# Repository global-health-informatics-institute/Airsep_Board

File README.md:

# Airsep_Board
Contains schematic design for the PCB, Eagle PCB design and MPLABX code

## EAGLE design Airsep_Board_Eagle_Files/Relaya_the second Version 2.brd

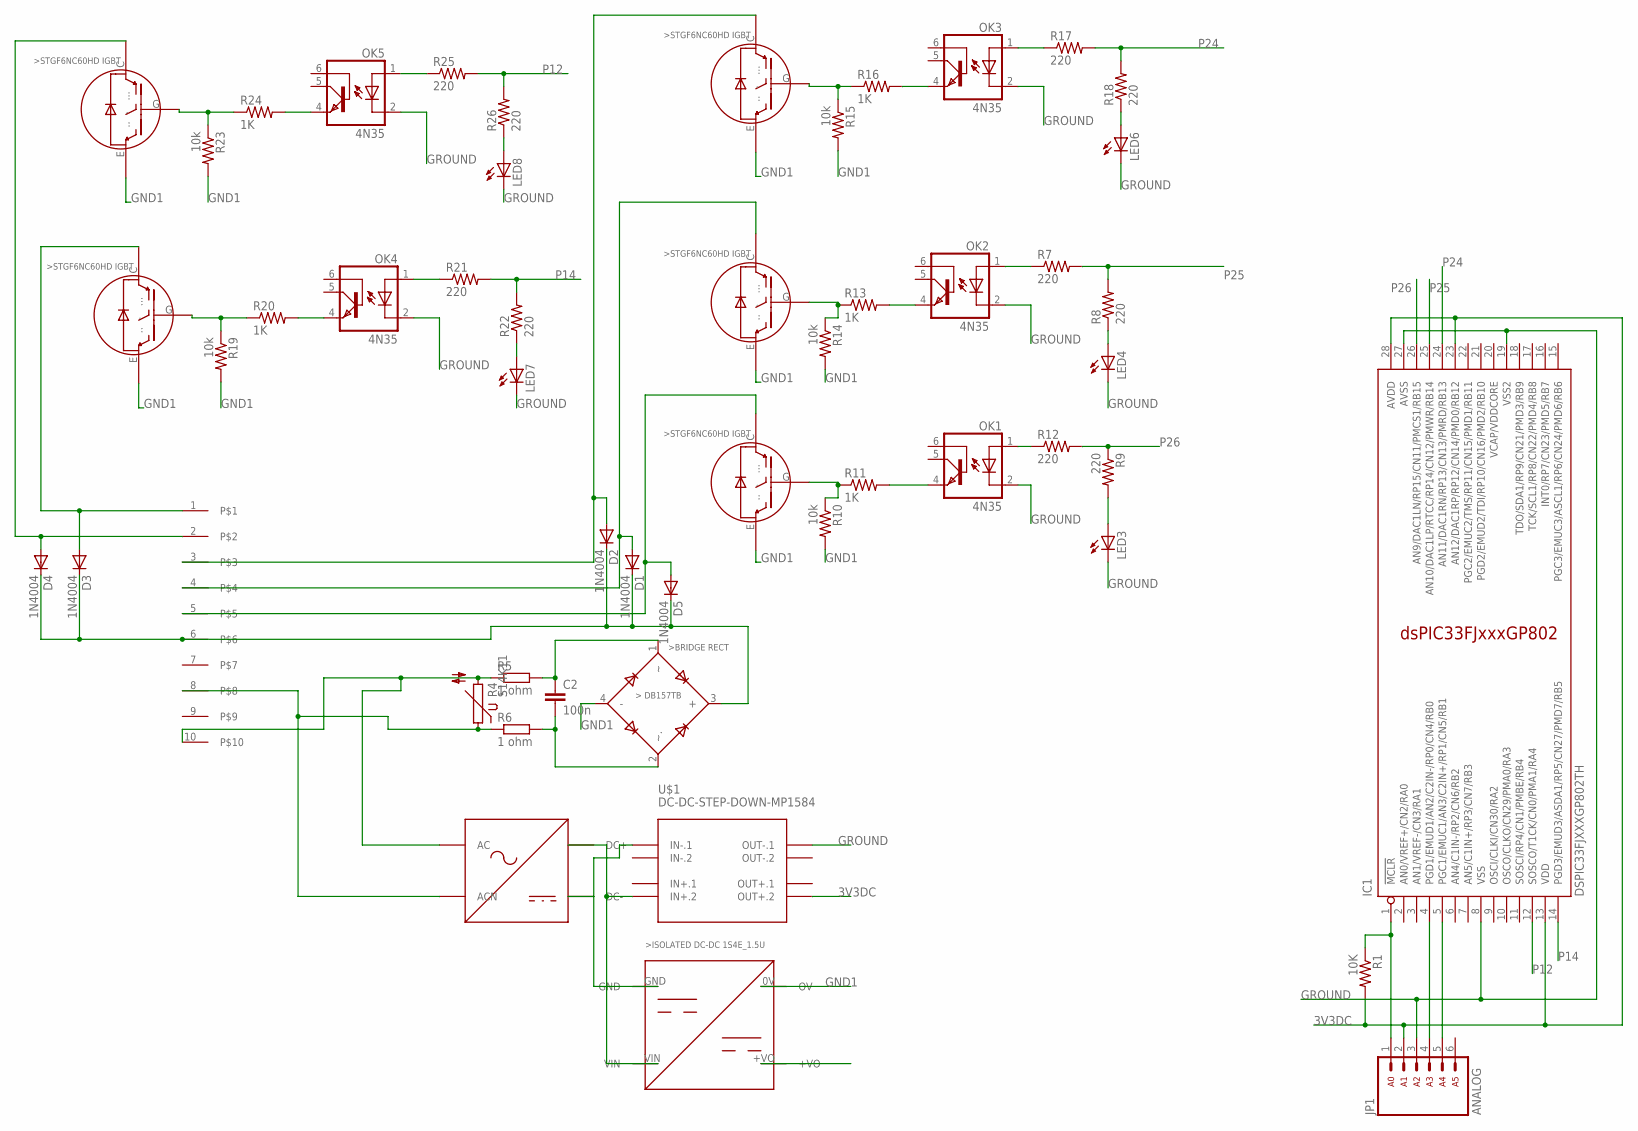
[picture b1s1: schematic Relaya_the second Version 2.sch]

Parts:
ASD1: MY_LIBRAY_RPD10W1S; MY_LIBRAY_2343
C2: 100n; C10B5
D1, D2, D3, D4, D5: 1N4004; DO41-10
IC1: DSPIC33FJXXXGP802TH; DIL28-3
JP1: ARDUINO_CONN-ANALOGSIP; CONN-1X06
LED3, LED4, LED6, LED7, LED8: LED5MM
OK1, OK2, OK3, OK4, OK5: 4N35; DIL06
R1: 10K; 0207/10
R4: S14K11
R5, R6: 1 ohm; 0617/17
R7, R8, R9, R12, R17, R18, R21, R22, R25, R26: 220; 0207/10
R10, R14, R15, R19, R23: 10k; 0207/10
R11, R13, R16, R20, R24: 1K; 0207/10
U$1: DC-DC-STEP-DOWN-MP1584
U$2: AIRSEP_POWER_CONNECTOR; JST-XH-CONNECTORS-GHII_JST-XH-10-PACKAGE-ROUND-PAD
U$3: 1S4E_1.5UA; 1S4E_1.5U
U$4, U$6, U$7, U$8, U$9: IGBT_STGF6NC60HDA; STGF6NC60HD
U$5: BRIDGE_RECT_DB157TBA; DB157TB

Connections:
3V3DC: IC1.13 (VDD), IC1.23 (AN12/DAC1RP/RP12/CN14/PMD0/RB12), IC1.28 (AVDD), JP1.2, R1.2, U$1.OUT+.2
AC_IN: ASD1.ACN, R4.1, R6.1, U$2.8
AC__IN: ASD1.AC, R4.2, R5.1, U$2.10
GND1: R10.2, R14.2, R15.2, R19.2, R23.2, U$3.0V (OV), U$4.E (..), U$5.4 (-), U$6.E (..), U$7.E (..), U$8.E (..), U$9.E (..)
GROUND: IC1.8 (VSS), IC1.19 (VSS2), IC1.27 (AVSS), JP1.3, LED3.K (C), LED4.K (C), LED6.K (C), LED7.K (C), LED8.K (C), OK1.2 (C), OK2.2 (C), OK3.2 (C), OK4.2 (C), OK5.2 (C), U$1.OUT-.1
unnamed: OK1.4 (EMI), R11.2
unnamed: C2.1, R5.2, U$5.1
unnamed: C2.2, R6.2, U$5.2 (~.)
unnamed: R10.1, R11.1, U$4.G (.)
unnamed: OK1.1 (A), R12.1
unnamed: LED3.A, R9.2
unnamed: R13.1, R14.1, U$6.G (.)
unnamed: OK2.1 (A), R7.1
unnamed: OK2.4 (EMI), R13.2
unnamed: LED4.A, R8.1
unnamed: OK3.4 (EMI), R16.2
unnamed: R15.1, R16.1, U$7.G (.)
unnamed: R19.1, R20.1, U$8.G (.)
unnamed: OK3.1 (A), R17.1
unnamed: LED6.A, R18.1
unnamed: OK4.4 (EMI), R20.2
unnamed: OK4.1 (A), R21.1
unnamed: LED7.A, R22.1
unnamed: R23.1, R24.1, U$9.G (.)
unnamed: OK5.4 (EMI), R24.2
unnamed: OK5.1 (A), R25.1
unnamed: LED8.A, R26.1
unnamed: D3.A, U$2.1, U$8.C (...)
unnamed: ASD1.DC+, U$1.IN+.2, U$3.VIN
unnamed: ASD1.DC-, U$1.IN-.1, U$3.GND
unnamed: D4.A, U$2.2, U$9.C (...)
unnamed: D2.A, U$2.3, U$7.C (...)
unnamed: D1.A, U$2.4, U$6.C (...)
unnamed: D5.A, U$2.5, U$4.C (...)
unnamed: D1.C, D2.C, D3.C, D4.C, D5.C, U$2.6, U$5.3 (+)
unnamed: IC1.5 (PGC1/EMUC1/AN3/C2IN+/RP1/CN5/RB1), JP1.5
unnamed: IC1.4 (PGD1/EMUD1/AN2/C2IN-/RP0/CN4/RB0), JP1.4
unnamed: IC1.1 (!MCLR), JP1.1, R1.1
P12: IC1.12 (SOSCO/T1CK/CN0/PMA1/RA4), R25.2, R26.2
P14: IC1.14 (PGD3/EMUD3/ASDA1/RP5/CN27/PMD7/RB5), R21.2, R22.2
P24: IC1.24 (AN11/DAC1RN/RP13/CN13/PMRD/RB13), R17.2, R18.2
P25: IC1.25 (AN10/DAC1LP/RTCC/RP14/CN12/PMWR/RB14), R7.2, R8.2
P26: IC1.26 (AN9/DAC1LN/RP15/CN11/PMCS1/RB15), R9.1, R12.2
VCAP/VDDCORE: IC1.20 (VCAP/VDDCORE)

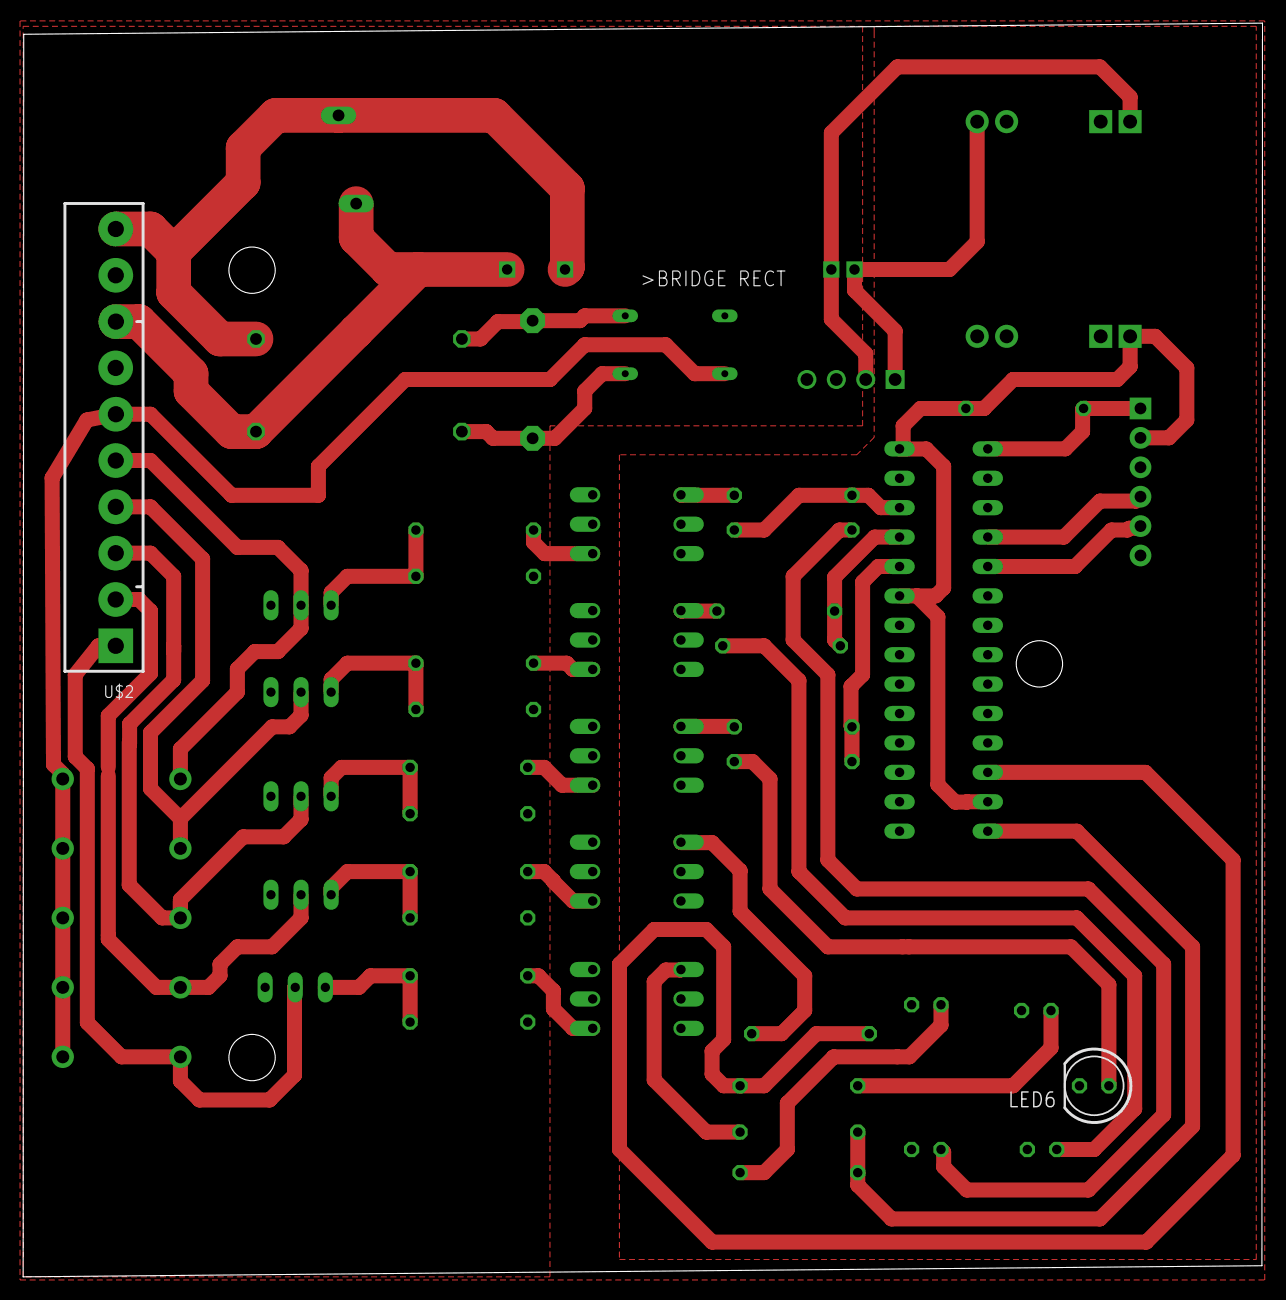
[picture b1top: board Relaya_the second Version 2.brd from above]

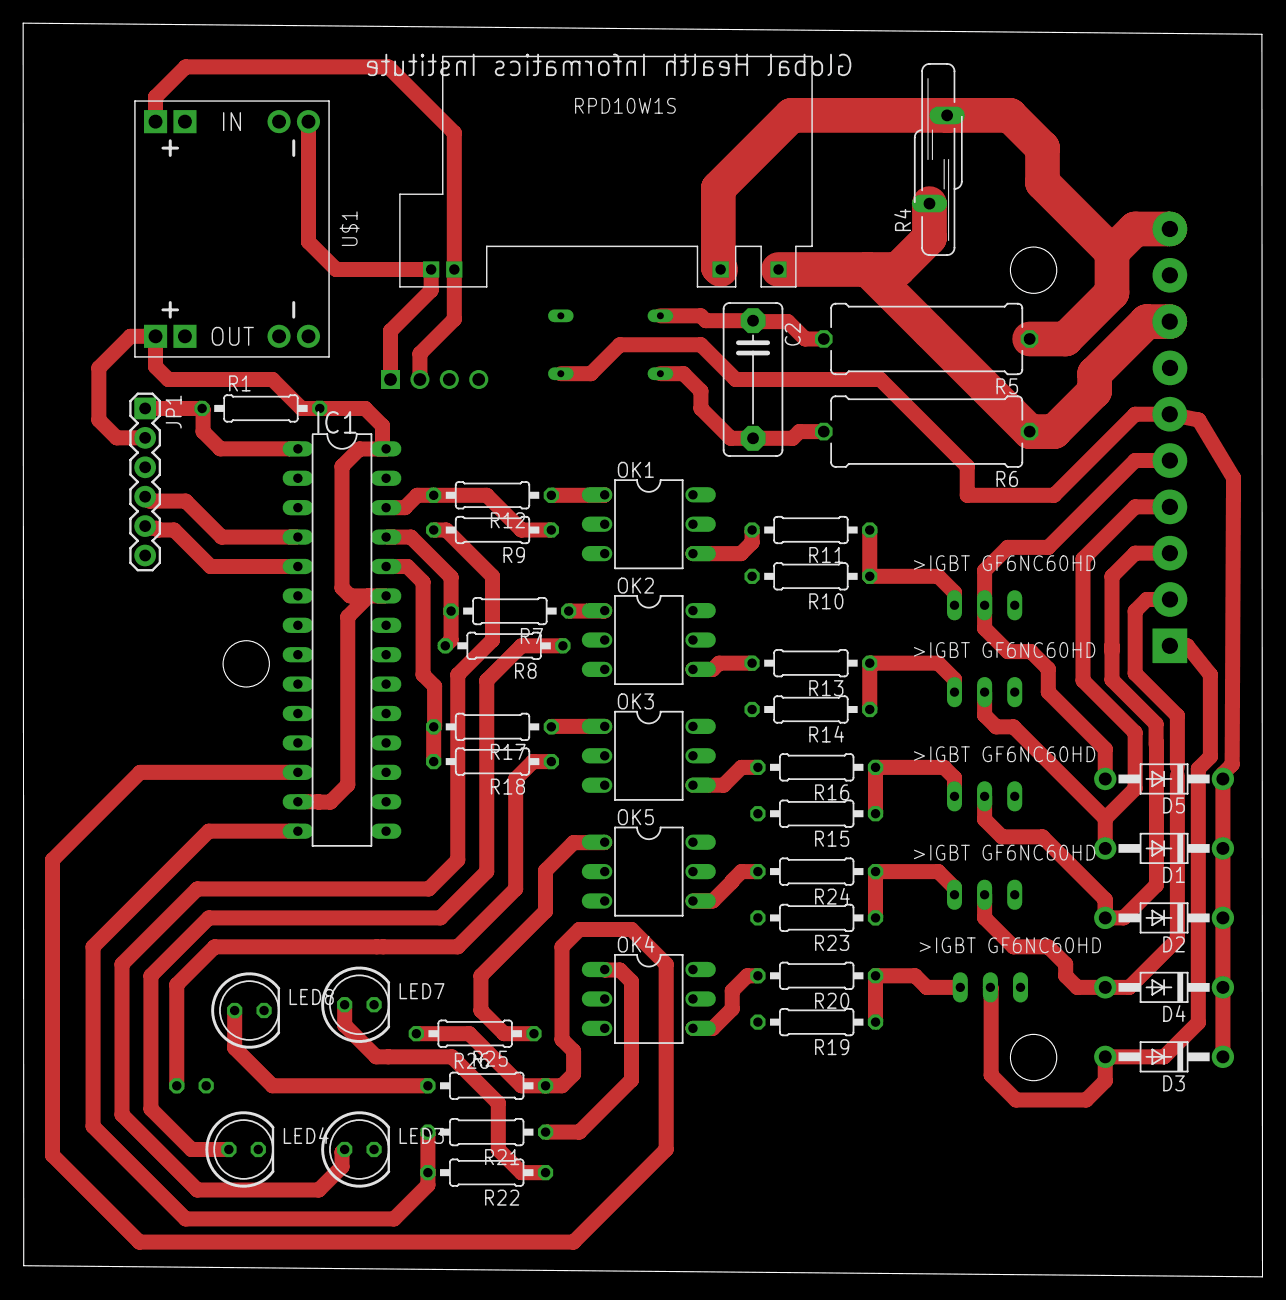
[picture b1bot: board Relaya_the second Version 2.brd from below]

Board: 2 copper layers, 107.0 x 108.3 mm, 52 parts (49 on the bottom side), 43 nets.

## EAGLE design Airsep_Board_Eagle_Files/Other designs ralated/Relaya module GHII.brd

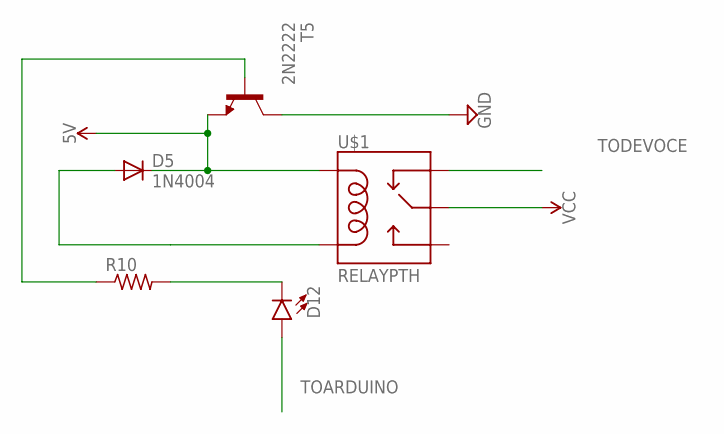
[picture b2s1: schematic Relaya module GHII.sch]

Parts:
D5: 1N4004; DO41-10
D12: LED5MM; LED_5MM
R10: R-US_0207/10; 0207/10
T5: 2N2222; TO92-EBC-OVAL
U$1: RELAYPTH; SRD-05VDC-SL-C

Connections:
GND: T5.C
unnamed: D12.K (C), R10.2
unnamed: R10.1, T5.B
unnamed: D5.A, U$1.COIL0
TOARDUINO: D12.A
TODEVOCE: U$1.SWCLOSED (SWCLOSE)
VCC: U$1.SWCOMMON
VCCIO: D5.C, T5.E, U$1.COIL1

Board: 2 copper layers, 5 parts (0 on the bottom side), 4 nets, no tracks yet.

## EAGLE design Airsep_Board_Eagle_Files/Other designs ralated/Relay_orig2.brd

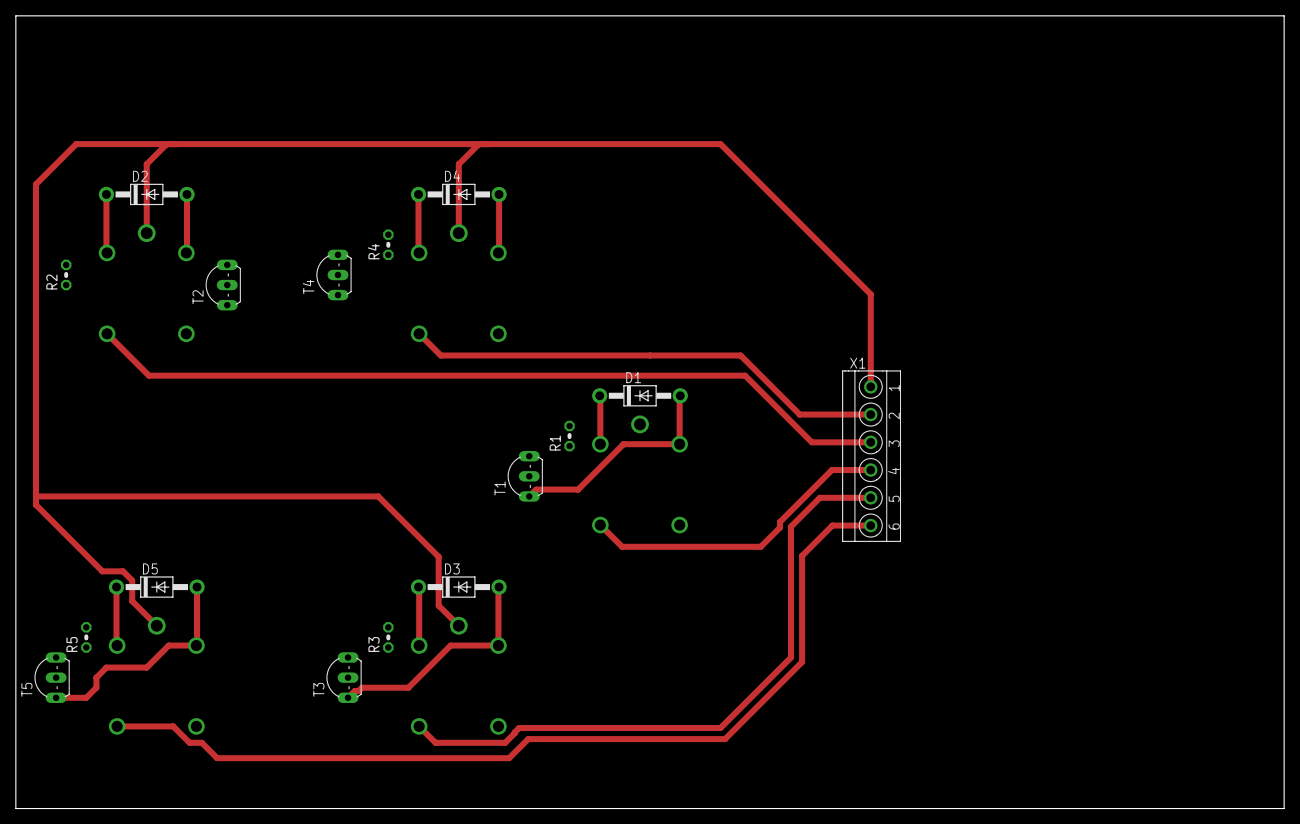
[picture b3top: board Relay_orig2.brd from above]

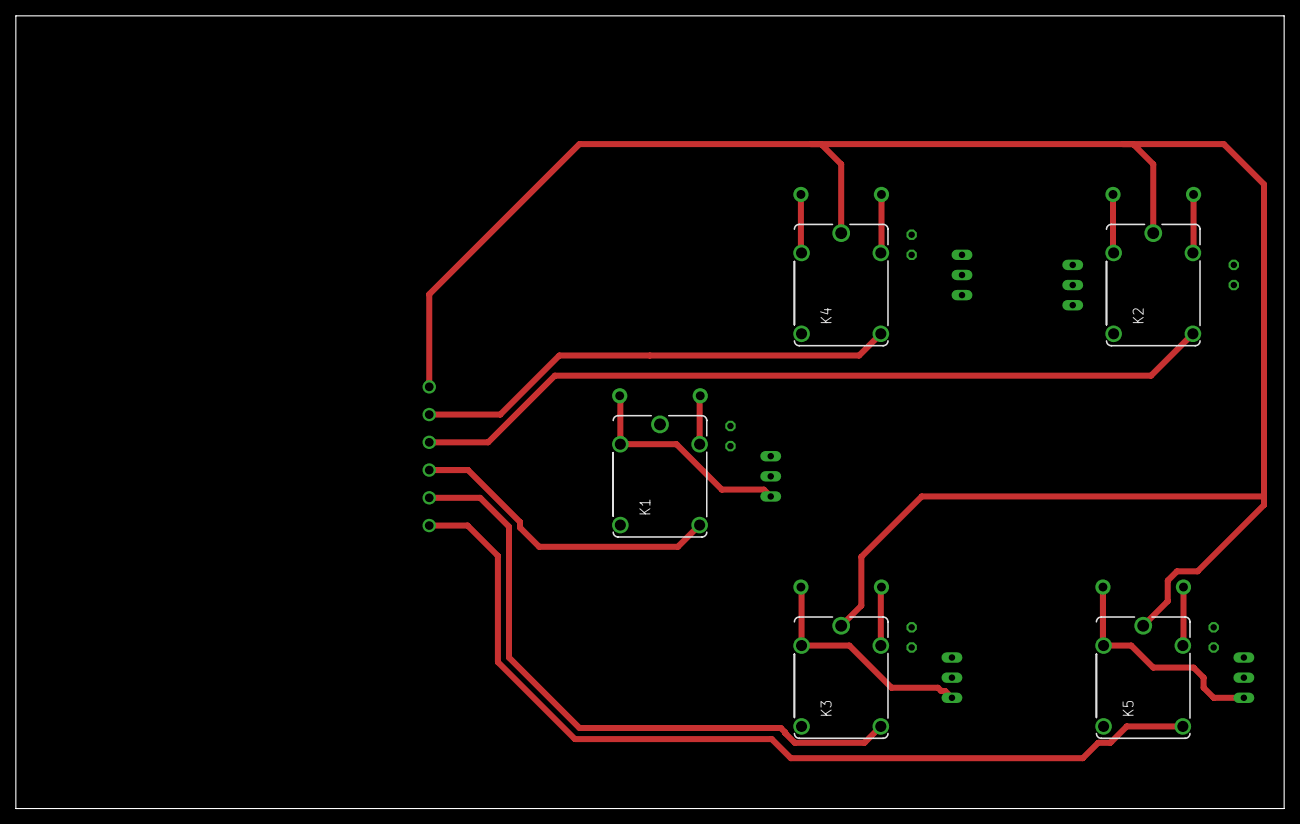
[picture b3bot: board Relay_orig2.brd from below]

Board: 2 copper layers, 160.0 x 100.0 mm, 21 parts (5 on the bottom side), 22 nets.

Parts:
D1, D2, D3, D4, D5: 1N4004; DO41-10
K1, K2, K3, K4, K5: JJM2W-5V; JJM
R1, R2, R3, R4, R5: 0204V
T1, T2, T3, T4, T5: 2N2222; TO92-EBC-OVAL
X1: TERMINAL-BLOCK-3.5MM-6-PIN-ROUND-PAD; TERMINAL-BLOCK-6-PIN-3.5MM-ROUND-PAD

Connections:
GND: T1.C, T2.C, T3.C, T4.C, T5.C
unnamed: D1.A, K1.1, T1.E
unnamed: R1.1, T1.B
unnamed: D2.A, K2.1, T2.E
unnamed: R3.1, T3.B
unnamed: R2.1, T2.B
unnamed: D2.C, K2.2
unnamed: D1.C, K1.2
unnamed: D3.C, K3.2
unnamed: D3.A, K3.1, T3.E
unnamed: D4.C, K4.2
unnamed: D4.A, K4.1, T4.E
unnamed: R4.1, T4.B
unnamed: R5.1, T5.B
unnamed: D5.C, K5.2
unnamed: D5.A, K5.1, T5.E
unnamed: K5.NO2, X1.6
unnamed: K3.NO2, X1.5
unnamed: K1.NO2, X1.4
unnamed: K4.NO2, X1.2
unnamed: K2.NO2, X1.3
VCCA: K1.C, K2.C, K3.C, K4.C, K5.C, X1.1

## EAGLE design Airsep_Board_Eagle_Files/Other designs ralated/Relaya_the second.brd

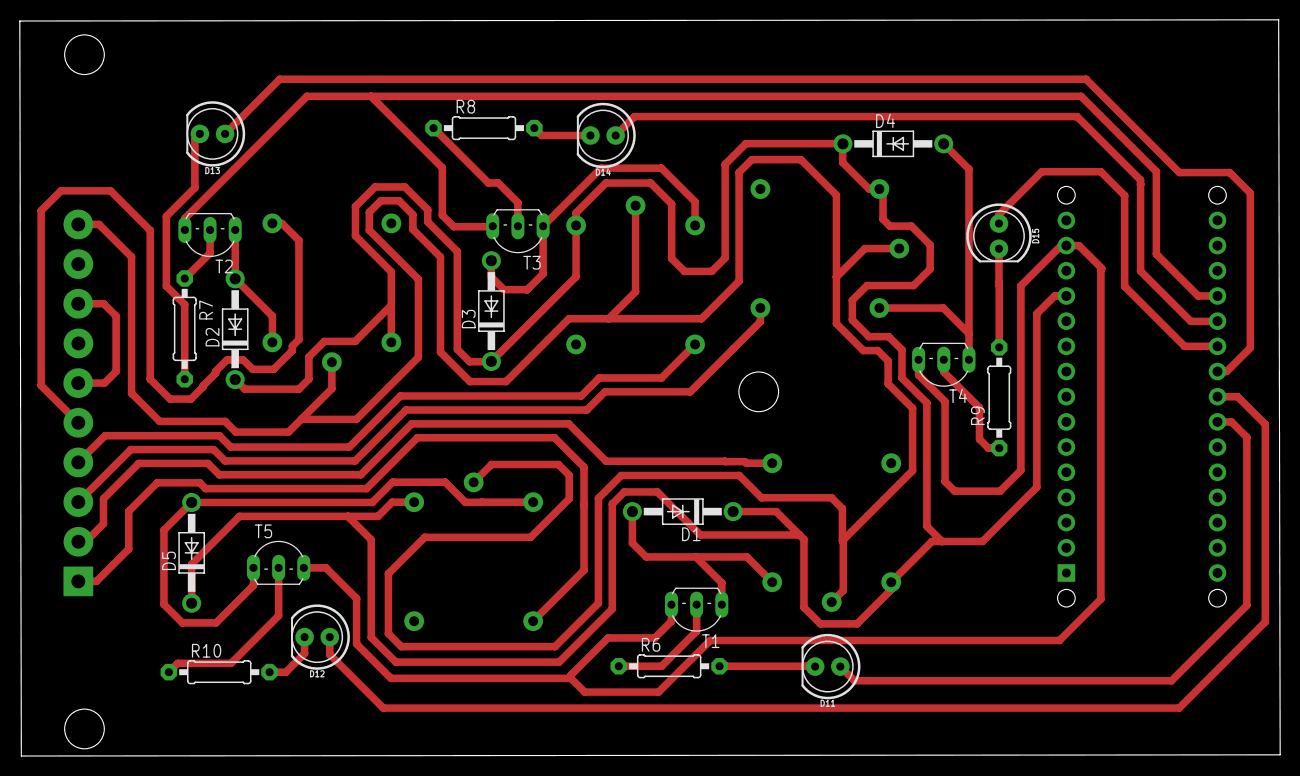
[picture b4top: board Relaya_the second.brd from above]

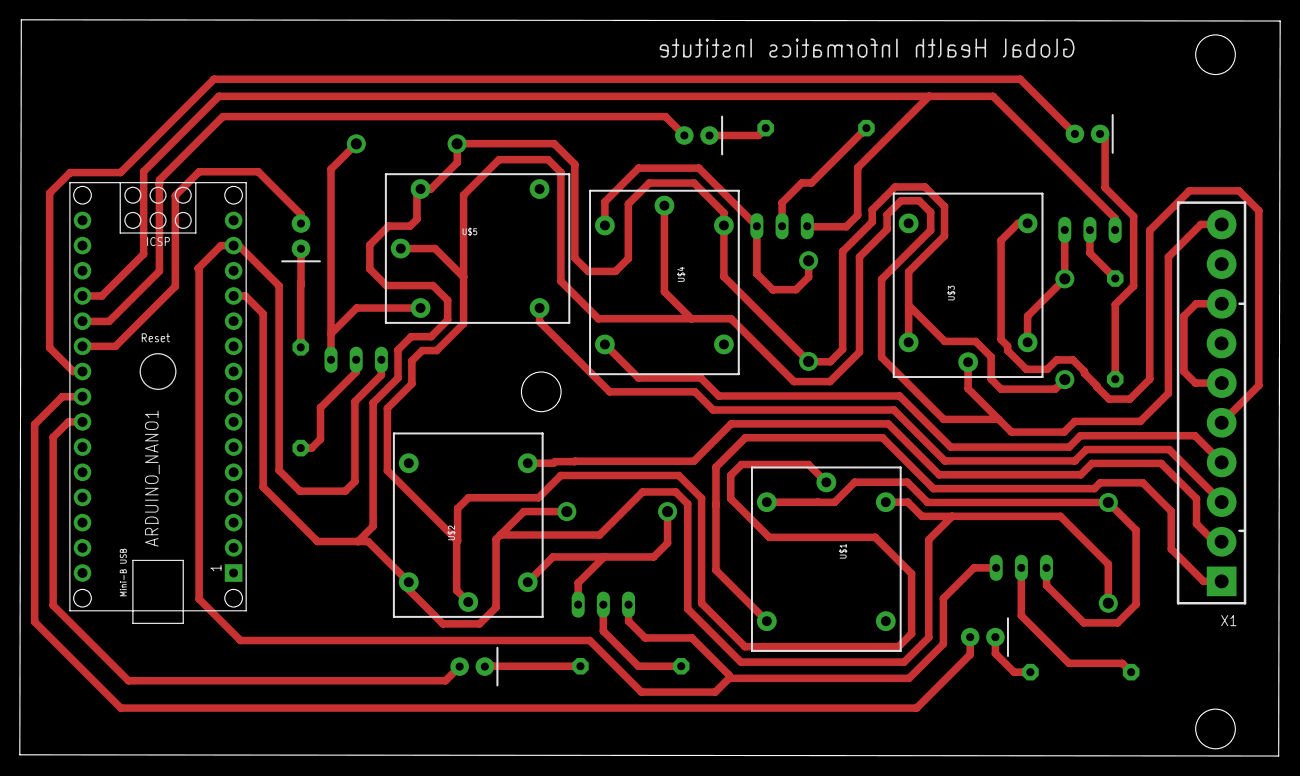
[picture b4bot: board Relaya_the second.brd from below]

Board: 2 copper layers, 127.1 x 74.2 mm, 27 parts (7 on the bottom side), 29 nets.

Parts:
ARDUINO_NANO1: ARDUINO_NANO
D1, D2, D3, D4, D5: 1N4004; DO41-10
D11, D12, D13, D14, D15: LED_5MM
R6, R7, R8, R9, R10: 0207/10
T1, T2, T3, T4, T5: 2N2222; TO92-EBC-OVAL
U$1, U$2, U$3, U$4, U$5: RELAYPTH; SRD-05VDC-SL-C
X1: JST-XH-10-PIN-ROUND-PAD; JST-XH-10-PACKAGE-ROUND-PAD

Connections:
5V: ARDUINO_NANO1.12, D1.C, D2.C, D3.C, D4.C, D5.C, U$1.COIL1, U$2.COIL1, U$3.COIL1, U$4.COIL1, U$5.COIL1
GND: ARDUINO_NANO1.14, ARDUINO_NANO1.19, T1.C, T2.C, T3.C, T4.C, T5.C
unnamed: U$1.SWCLOSED, X1.1
unnamed: ARDUINO_NANO1.23, D12.A
unnamed: R6.1, T1.B
unnamed: U$2.SWCLOSED, X1.2
unnamed: D1.A, T1.E, U$2.COIL0
unnamed: ARDUINO_NANO1.24, D11.A
unnamed: D2.A, T2.E, U$3.COIL0
unnamed: R7.1, T2.B
unnamed: ARDUINO_NANO1.22, D13.A
unnamed: U$3.SWCLOSED, X1.5
unnamed: D3.A, T3.E, U$4.COIL0
unnamed: R8.1, T3.B
unnamed: U$4.SWCLOSED, X1.4
unnamed: R10.1, T5.B
unnamed: X1.6, X1.8
unnamed: D5.A, T5.E, U$1.COIL0
unnamed: R9.1, T4.B
unnamed: ARDUINO_NANO1.20, D14.A
unnamed: D4.A, T4.E, U$5.COIL0
unnamed: U$5.SWCLOSED, X1.3
unnamed: ARDUINO_NANO1.21, D15.A
unnamed: D12.K, R10.2
unnamed: D11.K, R6.2
unnamed: D14.K, R8.2
unnamed: D13.K, R7.2
unnamed: D15.K, R9.2
VCC: U$1.SWCOMMON, U$2.SWCOMMON, U$3.SWCOMMON, U$4.SWCOMMON, U$5.SWCOMMON, X1.10

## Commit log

2021-12-06 removed build folder
2022-02-16 First Push

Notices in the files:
parts and their libraries:
SparkFun-LED: Licensing: Creative Commons ShareAlike 4.0 International - https://creativecommons.org/licenses/by-sa/4.0
GHIdiy-modules: Released under the Creative Commons Attribution 4.0 International License: http://creativecommons.org/licenses/by/4.0
